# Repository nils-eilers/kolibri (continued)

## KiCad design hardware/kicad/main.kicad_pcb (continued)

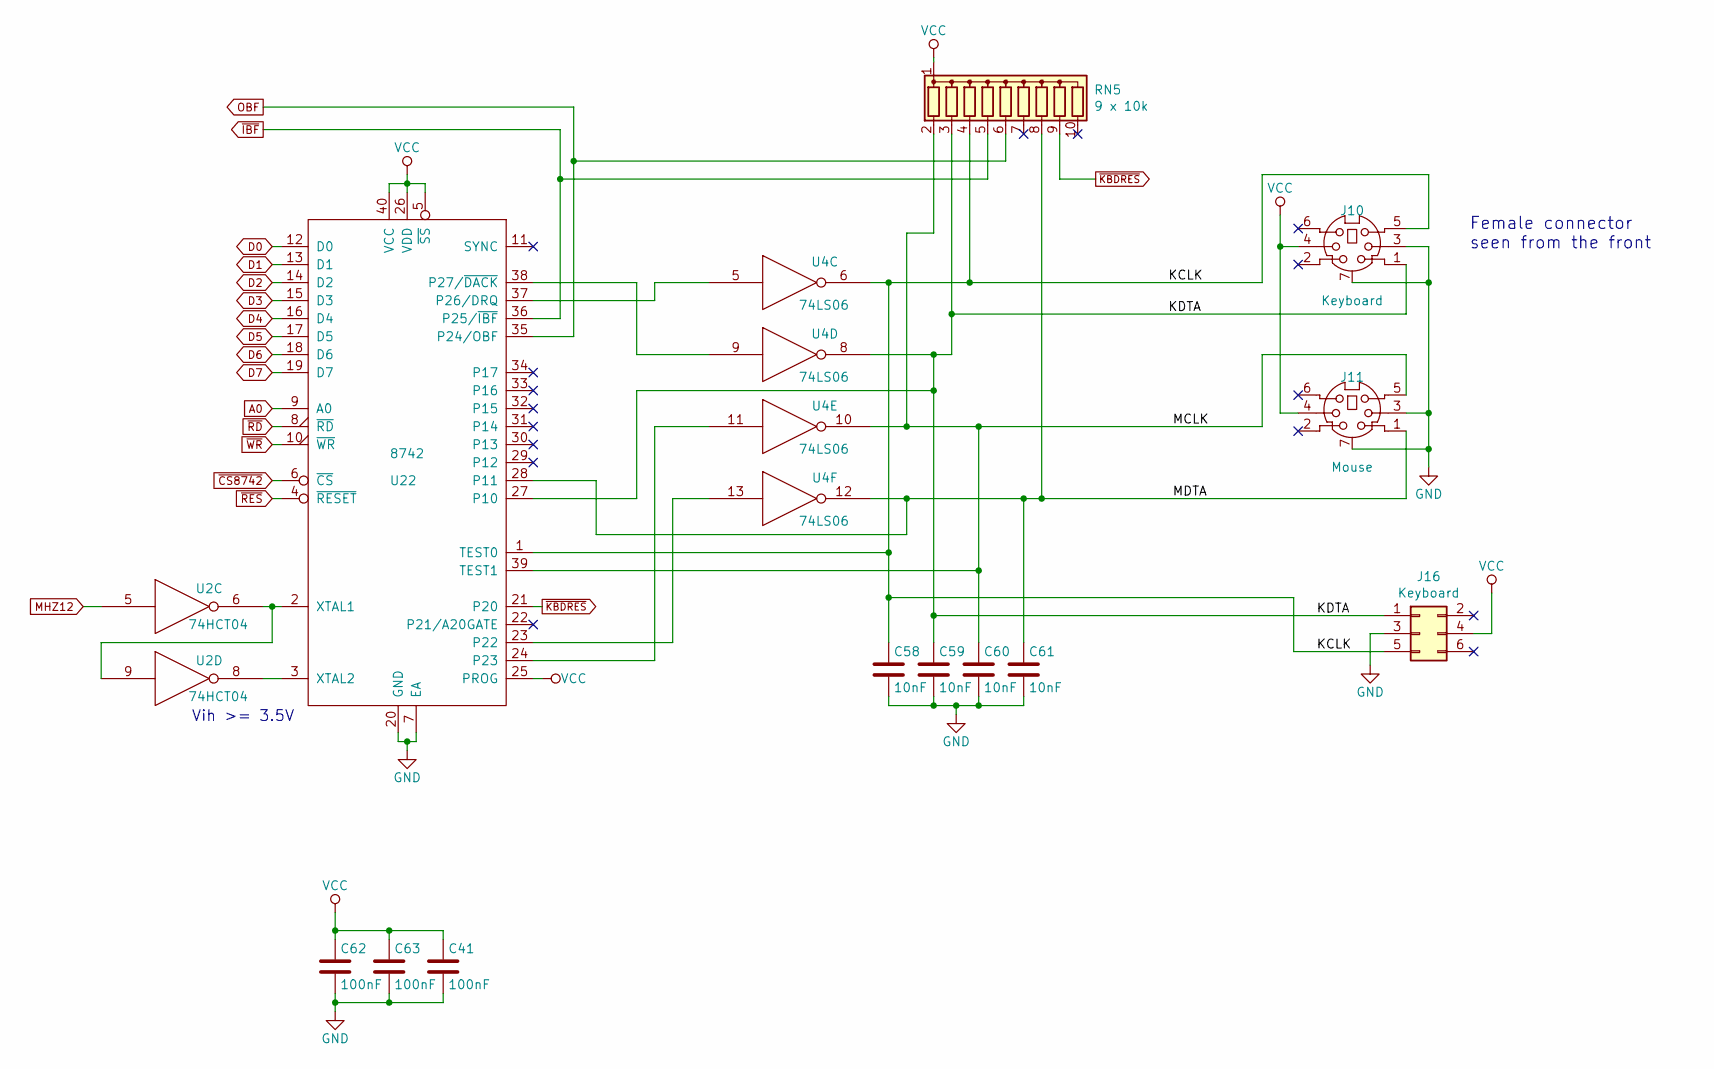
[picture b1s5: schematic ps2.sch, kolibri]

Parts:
C41, C62, C63: 100nF; KERKO-5
C58, C59, C60, C61: 10nF; KERKO-5
J10: Keyboard; EB-DIOS-M06
J11: Mouse; EB-DIOS-M06
J16: Keyboard; IDC-Header_2x03_P2.54mm_Vertical
RN5: 9 x 10k; R_Array_SIP10
U2: 74HCT04; DIP-14
U4: 74LS06; DIP-14
U22: 8742; DIP-40

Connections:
/Keyboard, Mouse/KCLK: C58.1, J10.5, J16.5, RN5.4 (R3), U4.6, U22.1 (TEST0)
/Keyboard, Mouse/KDTA: C59.1, J10.1, J16.1, RN5.3 (R2), U4.8, U22.27 (P10)
/Keyboard, Mouse/MCLK: C60.1, J11.5, RN5.2 (R1), U4.10, U22.39 (TEST1)
/Keyboard, Mouse/MDTA: C61.1, J11.1, RN5.8 (R7), U4.12, U22.28 (P11)
A0: U22.9 (A0); also elsewhere on the board
D0: U22.12 (D0); also elsewhere on the board
D1: U22.13 (D1); also elsewhere on the board
D2: U22.14 (D2); also elsewhere on the board
D3: U22.15 (D3); also elsewhere on the board
D4: U22.16 (D4); also elsewhere on the board
D5: U22.17 (D5); also elsewhere on the board
D6: U22.18 (D6); also elsewhere on the board
D7: U22.19 (D7); also elsewhere on the board
GND: C41.2, C58.2, C59.2, C60.2, C61.2, C62.2, C63.2, J10.3, J10.7 (Shell), J11.3, J11.7 (Shell), J16.3, U2.7 (GND), U4.7 (GND), U22.7 (EA), U22.20 (GND); also elsewhere on the board
MHZ12: U2.5; also elsewhere on the board
unnamed: U2.6, U2.9, U22.2 (XTAL1)
unnamed: U2.8, U22.3 (XTAL2)
unnamed: U4.13, U22.23 (P22)
unnamed: U4.11, U22.24 (P23)
unnamed: U4.5, U22.37 (P26/DRQ)
unnamed: U4.9, U22.38 (P27/~DACK)
OBF: RN5.6 (R5), U22.35 (P24/OBF); also elsewhere on the board
VCC: C41.1, C62.1, C63.1, J10.4, J11.4, J16.4, RN5.1 (common), U2.14 (VCC), U4.14 (VCC), U22.5 (~SS~), U22.25 (PROG), U22.26 (VDD), U22.40 (VCC); also elsewhere on the board
~CS8742: U22.6 (~CS); also elsewhere on the board
~IBF: RN5.5 (R4), U22.36 (P25/~IBF); also elsewhere on the board
~KBDRES: RN5.9 (R8), U22.21 (P20); also elsewhere on the board
~RD: U22.8 (~RD~); also elsewhere on the board
~RES: U22.4 (~RESET~); also elsewhere on the board
~WR: U22.10 (~WR~); also elsewhere on the board

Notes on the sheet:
Vih >= 3.5V
Female connector seen from the front

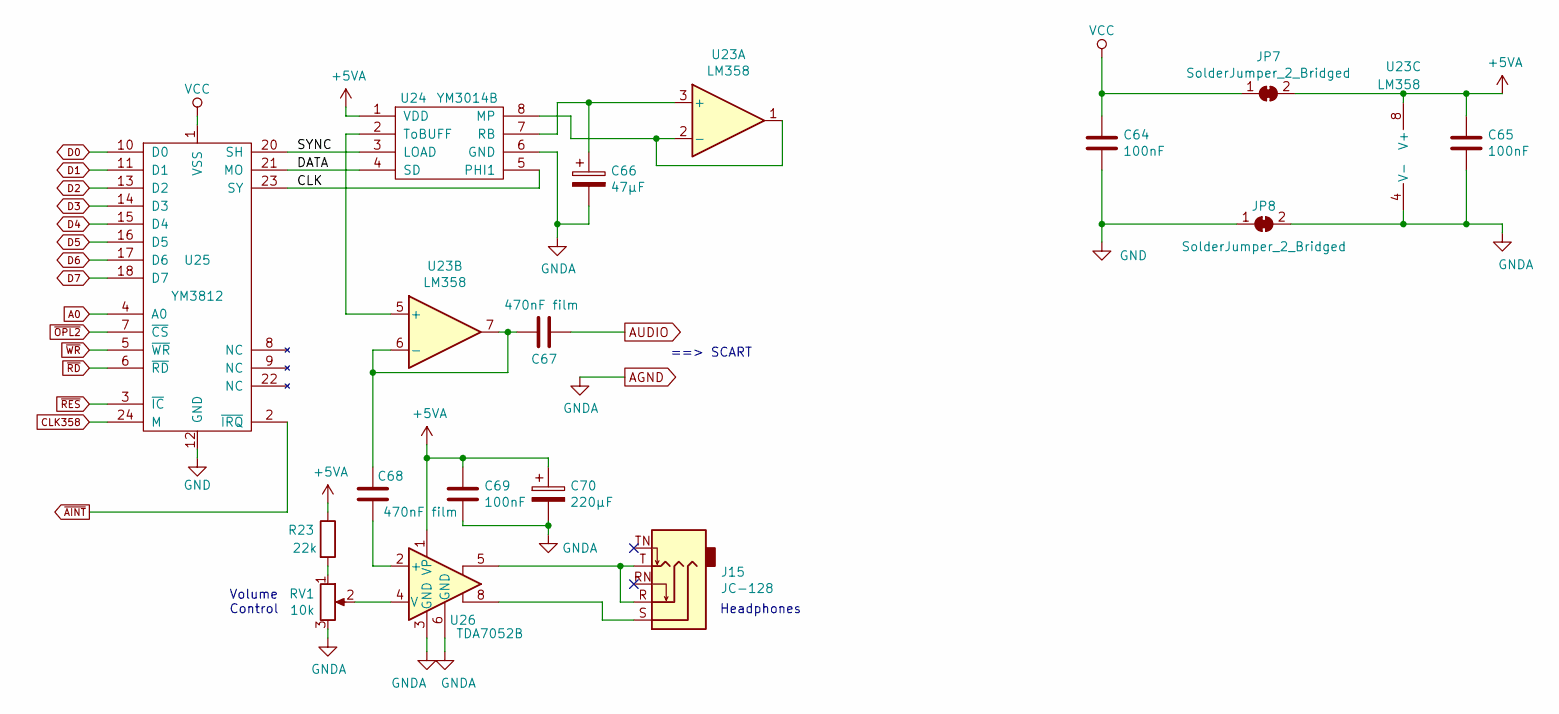
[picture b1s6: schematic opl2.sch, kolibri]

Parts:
C64, C65, C69: 100nF; KERKO-5
C66: 47µF; CP-2-5
C67, C68: 470nF film; C-FILM-5
C70: 220µF; CP-2-6
J15: JC-128
JP7, JP8: SolderJumper_2_Bridged; SolderJumper-2_P1.3mm_Bridged_RoundedPad1.0x1.5mm
R23: 22k; R
RV1: 10k; PT10H-THUMBWHEEL
U23: LM358; DIP-8
U24: YM3014B; DIP-8
U25: YM3812; DIP-24
U26: TDA7052B; DIP-8

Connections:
+5VA: C65.1, C69.1, C70.1, JP7.2 (B), R23.1, U23.8 (V+), U24.1 (VDD), U26.1 (VP)
/OPL2 sound/CLK: U24.5 (PHI1), U25.23 (SY)
/OPL2 sound/DATA: U24.4 (SD), U25.21 (MO)
/OPL2 sound/SYNC: U24.3 (LOAD), U25.20 (SH)
A0: U25.4 (A0); also elsewhere on the board
AGND: C65.2, C66.2, C69.2, C70.2, JP8.2 (B), RV1.3, U23.4 (V-), U24.6 (GND), U26.3 (GND), U26.6 (GND); also elsewhere on the board
AUDIO: C67.1; also elsewhere on the board
CLK358: U25.24 (M); also elsewhere on the board
D0: U25.10 (D0); also elsewhere on the board
D1: U25.11 (D1); also elsewhere on the board
D2: U25.13 (D2); also elsewhere on the board
D3: U25.14 (D3); also elsewhere on the board
D4: U25.15 (D4); also elsewhere on the board
D5: U25.16 (D5); also elsewhere on the board
D6: U25.17 (D6); also elsewhere on the board
D7: U25.18 (D7); also elsewhere on the board
GND: C64.2, JP8.1 (A), U25.12 (GND); also elsewhere on the board
unnamed: C66.1, U23.3 (+), U24.7 (RB)
unnamed: C67.2, C68.2, U23.6 (-), U23.7
unnamed: C68.1, U26.2 (+)
unnamed: J15.R, J15.T, U26.5
unnamed: J15.S, U26.8
unnamed: R23.2, RV1.1
unnamed: RV1.2, U26.4 (V)
unnamed: U23.1, U23.2 (-), U24.8 (MP)
unnamed: U23.5 (+), U24.2 (ToBUFF)
VCC: C64.1, JP7.1 (A), U25.1 (VSS); also elsewhere on the board
~AINT: U25.2 (~IRQ); also elsewhere on the board
~OPL2: U25.7 (~CS); also elsewhere on the board
~RD: U25.6 (~RD); also elsewhere on the board
~RES: U25.3 (~IC); also elsewhere on the board
~WR: U25.5 (~WR); also elsewhere on the board

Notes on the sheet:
==> SCART
Headphones
Volume Control

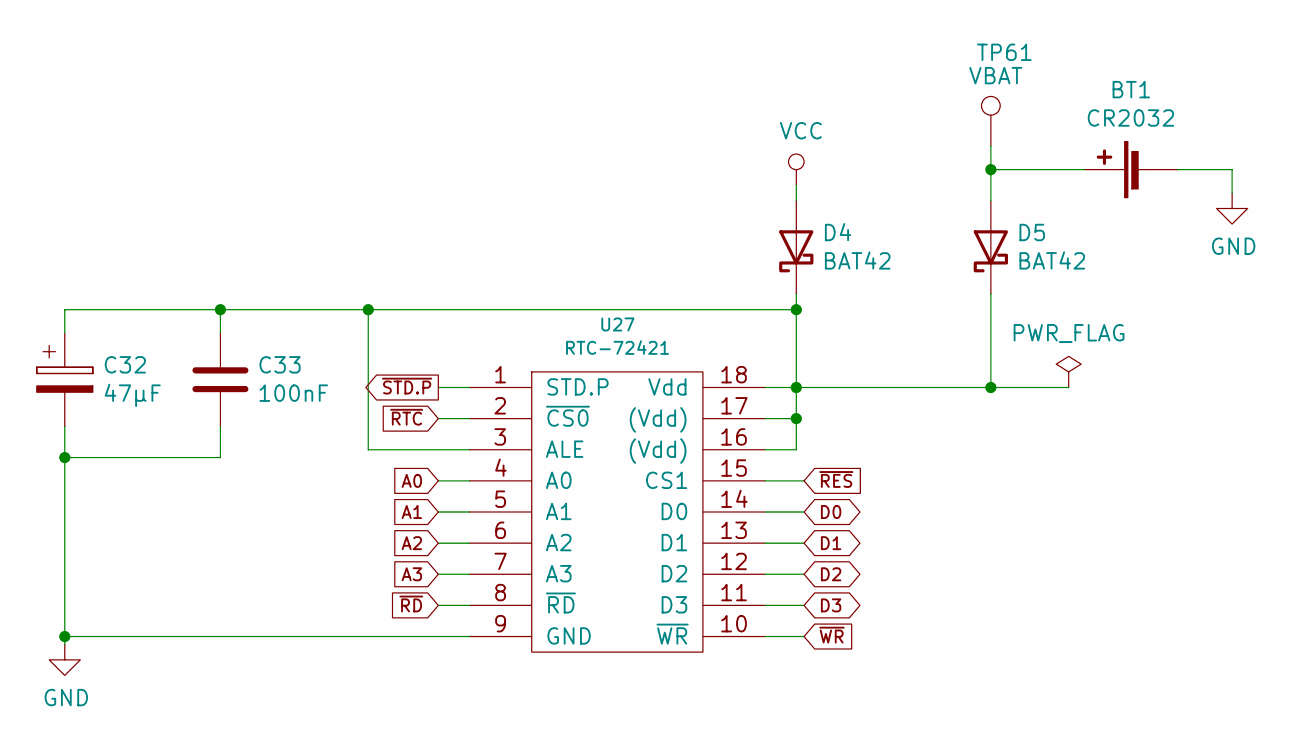
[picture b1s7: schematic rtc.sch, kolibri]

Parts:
BT1: CR2032; KZH20SMD
C32: 47µF; CP-2-5
C33: 100nF; KERKO-5
D4, D5: BAT42; DO35
TP61: VBAT; PINTST
U27: RTC-72421; DIP-18

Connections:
A0: U27.4 (A0); also elsewhere on the board
A1: U27.5 (A1); also elsewhere on the board
A2: U27.6 (A2); also elsewhere on the board
A3: U27.7 (A3); also elsewhere on the board
D0: U27.14 (D0); also elsewhere on the board
D1: U27.13 (D1); also elsewhere on the board
D2: U27.12 (D2); also elsewhere on the board
D3: U27.11 (D3); also elsewhere on the board
GND: BT1.2 (-), C32.2, C33.2, U27.9 (GND); also elsewhere on the board
unnamed: BT1.1 (+), D5.2 (A), TP61.1
unnamed: C32.1, C33.1, D4.1 (K), D5.1 (K), U27.3 (ALE), U27.16 ((Vdd)), U27.17 ((Vdd)), U27.18 (Vdd)
VCC: D4.2 (A); also elsewhere on the board
~RD: U27.8 (~RD); also elsewhere on the board
~RES: U27.15 (CS1); also elsewhere on the board
~RTC: U27.2 (~CS0); also elsewhere on the board
~STD.P: U27.1 (STD.P); also elsewhere on the board
~WR: U27.10 (~WR); also elsewhere on the board

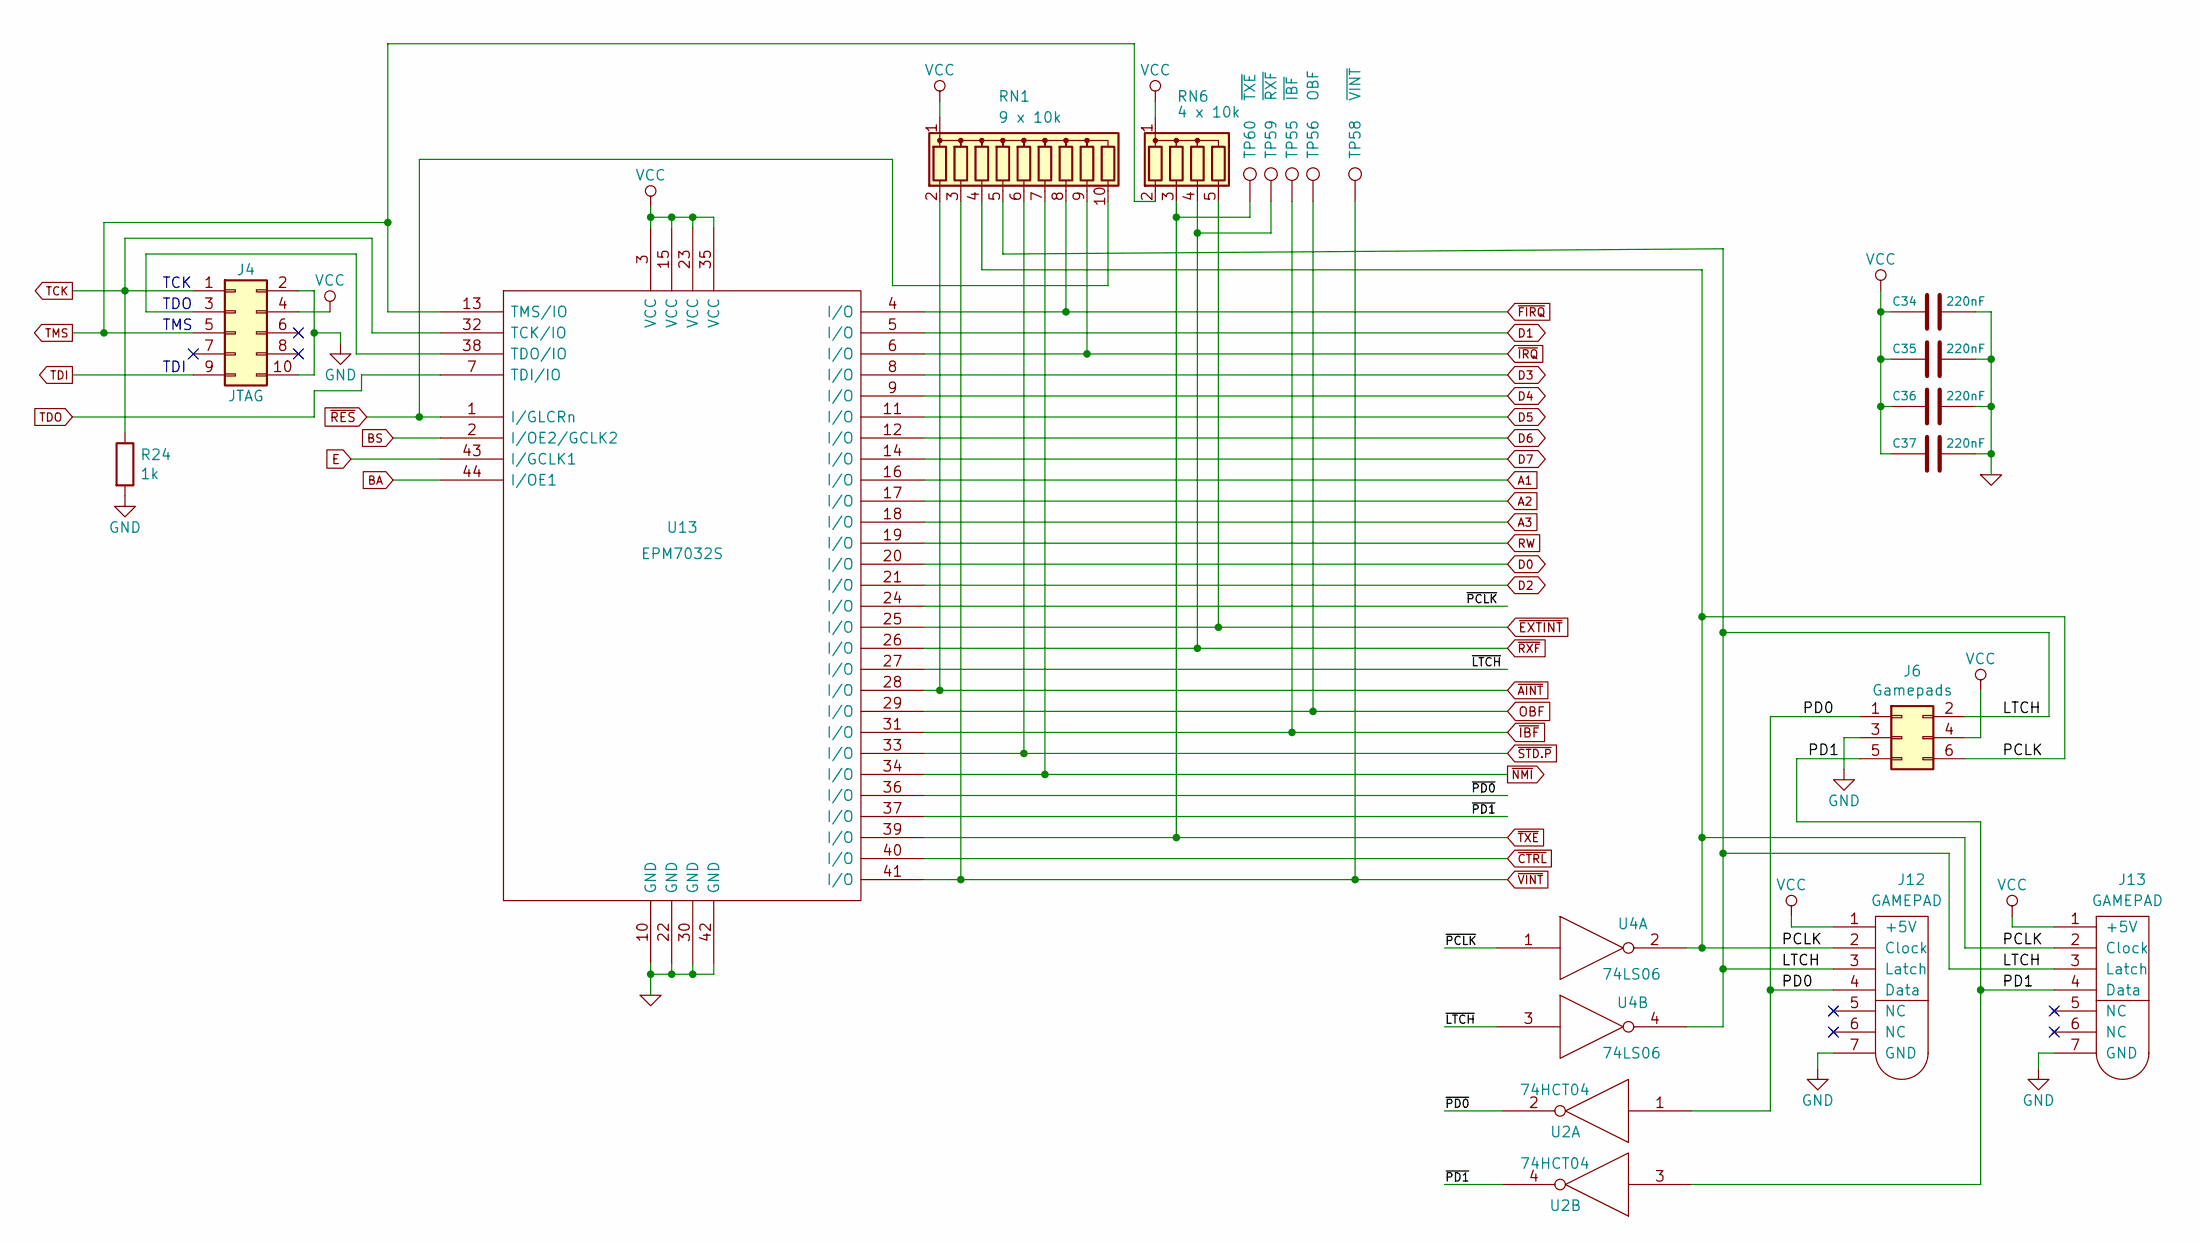
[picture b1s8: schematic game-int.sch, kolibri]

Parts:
C34, C35, C36, C37: 220nF; KERKO-5
J4: JTAG; WSL10G
J6: Gamepads; WSL_6W
J12, J13: GAMEPAD
R24: 1k; R
RN1: 9 x 10k; R_Array_SIP10
RN6: 4 x 10k; R_Array_SIP5
TP55: ~IBF; PINTST
TP56: OBF; PINTST
TP58: ~VINT; PINTST
TP59: ~RXF; PINTST
TP60: ~TXE; PINTST
U2: 74HCT04; DIP-14
U4: 74LS06; DIP-14
U13: EPM7032S; PLCC-44

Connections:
/Gamepads and Interrupts/LTCH: J6.2, J12.3 (Latch), J13.3 (Latch), RN1.5 (R4), U4.4
/Gamepads and Interrupts/PCLK: J6.6, J12.2 (Clock), J13.2 (Clock), RN1.4 (R3), U4.2
/Gamepads and Interrupts/PD0: J6.1, J12.4 (Data), U2.1
/Gamepads and Interrupts/PD1: J6.5, J13.4 (Data), U2.3
/Gamepads and Interrupts/~LTCH: U4.3, U13.27 (I/O)
/Gamepads and Interrupts/~PCLK: U4.1, U13.24 (I/O)
/Gamepads and Interrupts/~PD0: U2.2, U13.36 (I/O)
/Gamepads and Interrupts/~PD1: U2.4, U13.37 (I/O)
A1: U13.16 (I/O); also elsewhere on the board
A2: U13.17 (I/O); also elsewhere on the board
A3: U13.18 (I/O); also elsewhere on the board
BA: U13.44 (I/OE1); also elsewhere on the board
BS: U13.2 (I/OE2/GCLK2); also elsewhere on the board
D0: U13.20 (I/O); also elsewhere on the board
D1: U13.5 (I/O); also elsewhere on the board
D2: U13.21 (I/O); also elsewhere on the board
D3: U13.8 (I/O); also elsewhere on the board
D4: U13.9 (I/O); also elsewhere on the board
D5: U13.11 (I/O); also elsewhere on the board
D6: U13.12 (I/O); also elsewhere on the board
D7: U13.14 (I/O); also elsewhere on the board
E: U13.43 (I/GCLK1); also elsewhere on the board
GND: C34.2, C35.2, C36.2, C37.2, J4.2, J4.10, J6.3, J12.7 (GND), J13.7 (GND), R24.2, U2.7 (GND), U4.7 (GND), U13.10 (GND), U13.22 (GND), U13.30 (GND), U13.42 (GND); also elsewhere on the board
unnamed: J4.3, U13.38 (TDO/IO)
OBF: TP56.1, U13.29 (I/O); also elsewhere on the board
RW: U13.19 (I/O)
TCK: J4.1, R24.1, U13.32 (TCK/IO); also elsewhere on the board
TDI: J4.9; also elsewhere on the board
TDO: U13.7 (TDI/IO); also elsewhere on the board
TMS: J4.5, RN6.2 (R1), U13.13 (TMS/IO); also elsewhere on the board
VCC: C34.1, C35.1, C36.1, C37.1, J4.4, J6.4, J12.1 (+5V), J13.1 (+5V), RN1.1 (common), RN6.1 (common), U2.14 (VCC), U4.14 (VCC), U13.3 (VCC), U13.15 (VCC), U13.23 (VCC), U13.35 (VCC); also elsewhere on the board
~AINT: RN1.2 (R1), U13.28 (I/O); also elsewhere on the board
~CTRL: U13.40 (I/O); also elsewhere on the board
~EXTINT: RN6.5 (R4), U13.25 (I/O); also elsewhere on the board
~FIRQ: RN1.8 (R7), U13.4 (I/O); also elsewhere on the board
~IBF: TP55.1, U13.31 (I/O); also elsewhere on the board
~IRQ: RN1.9 (R8), U13.6 (I/O); also elsewhere on the board
~NMI: RN1.7 (R6), U13.34 (I/O); also elsewhere on the board
~RES: RN1.10 (R9), U13.1 (I/GLCRn); also elsewhere on the board
~RXF: RN6.4 (R3), TP59.1, U13.26 (I/O); also elsewhere on the board
~STD.P: RN1.6 (R5), U13.33 (I/O); also elsewhere on the board
~TXE: RN6.3 (R2), TP60.1, U13.39 (I/O); also elsewhere on the board
~VINT: RN1.3 (R2), TP58.1, U13.41 (I/O); also elsewhere on the board

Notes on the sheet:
TCK
TDO
TMS
TDI

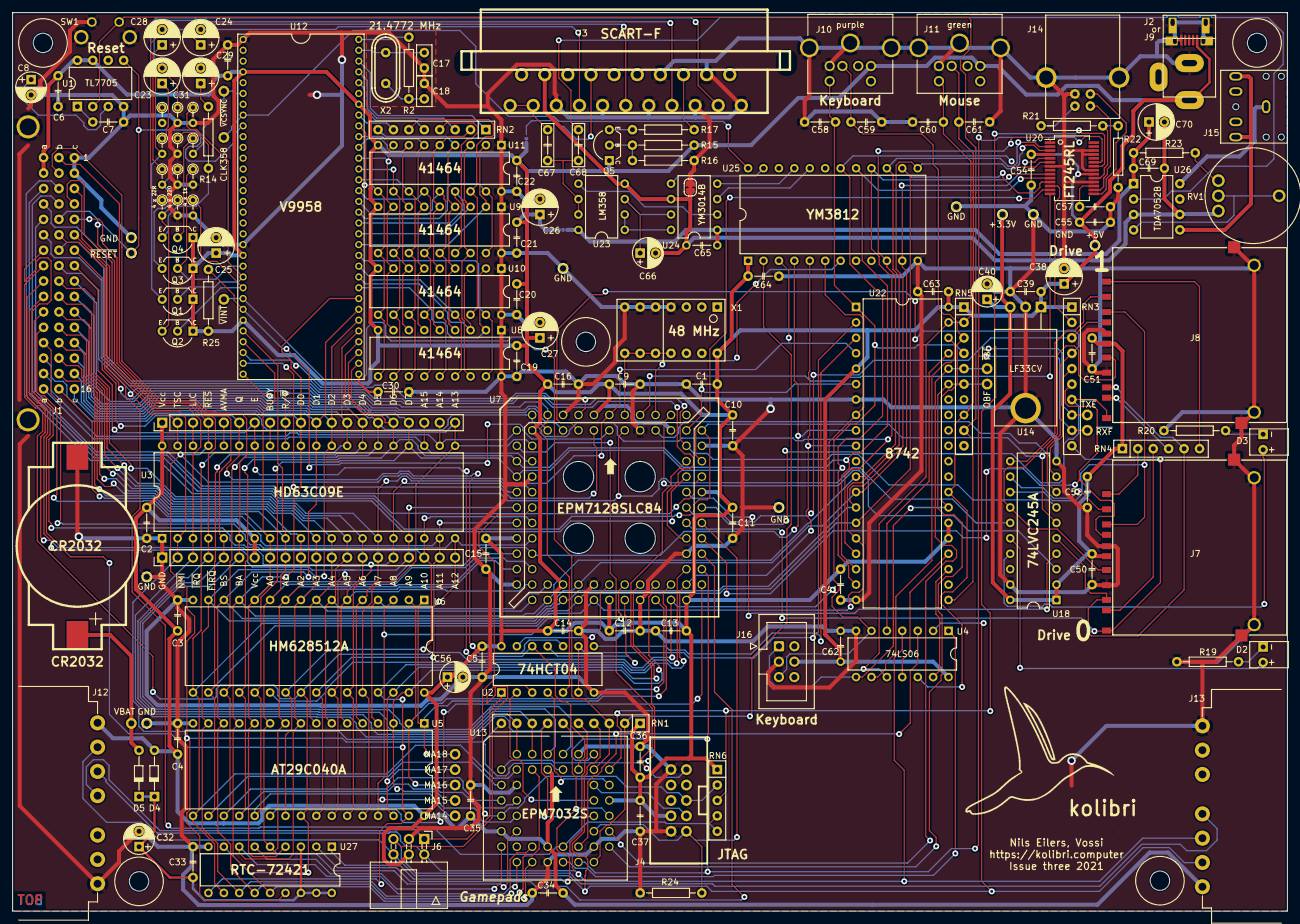
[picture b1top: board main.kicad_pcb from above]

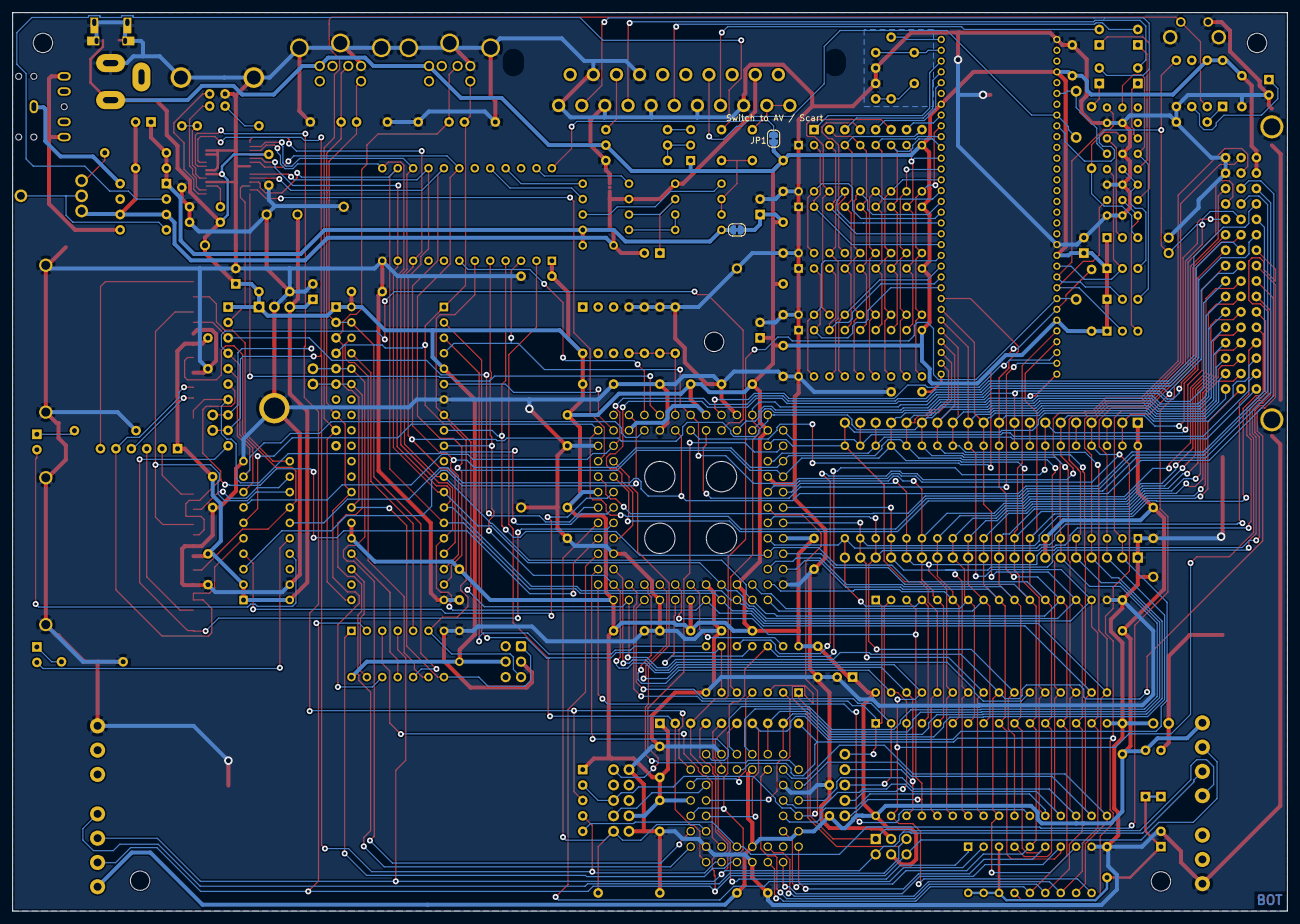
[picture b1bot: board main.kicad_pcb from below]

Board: 2 copper layers, 210.0 x 148.0 mm, 175 parts (2 on the bottom side), 196 nets.

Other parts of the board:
MH1, MH2, MH3, MH4, MH5: M3x6 + DI 8MM; M3-MOUNTHOLE

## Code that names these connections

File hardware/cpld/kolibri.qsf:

# -------------------------------------------------------------------------- #
#
# Copyright (C) 1991-2013 Altera Corporation
# Your use of Altera Corporation's design tools, logic functions 
# and other software and tools, and its AMPP partner logic 
# functions, and any output files from any of the foregoing 
# (including device programming or simulation files), and any 
# associated documentation or information are expressly subject 
# to the terms and conditions of the Altera Program License 
# Subscription Agreement, Altera MegaCore Function License 
# Agreement, or other applicable license agreement, including, 
# without limitation, that your use is for the sole purpose of 
# programming logic devices manufactured by Altera and sold by 
# Altera or its authorized distributors.  Please refer to the 
# applicable agreement for further details.
#
# -------------------------------------------------------------------------- #
#
# Quartus II 64-Bit
# Version 13.0.1 Build 232 06/12/2013 Service Pack 1 SJ Web Edition
# Date created = 00:44:14  April 05, 2018
#
# -------------------------------------------------------------------------- #
#
# Notes:
#
# 1) The default values for assignments are stored in the file:
#		kolibri_assignment_defaults.qdf
#    If this file doesn't exist, see file:
#		assignment_defaults.qdf
#
# 2) Altera recommends that you do not modify this file. This
#    file is updated automatically by the Quartus II software
#    and any changes you make may be lost or overwritten.
#
# -------------------------------------------------------------------------- #


set_global_assignment -name FAMILY MAX7000S
set_global_assignment -name DEVICE "EPM7128SLC84-15"
set_global_assignment -name TOP_LEVEL_ENTITY kolibri
set_global_assignment -name ORIGINAL_QUARTUS_VERSION "13.0 SP1"
set_global_assignment -name PROJECT_CREATION_TIME_DATE "00:44:14  APRIL 05, 2018"
set_global_assignment -name LAST_QUARTUS_VERSION "13.0 SP1"
set_global_assignment -name PROJECT_OUTPUT_DIRECTORY output_files
set_global_assignment -name DEVICE_FILTER_PACKAGE PLCC
set_global_assignment -name DEVICE_FILTER_PIN_COUNT 84
set_global_assignment -name ERROR_CHECK_FREQUENCY_DIVISOR "-1"
set_global_assignment -name MIN_CORE_JUNCTION_TEMP 0
set_global_assignment -name MAX_CORE_JUNCTION_TEMP 85
set_global_assignment -name EDA_SIMULATION_TOOL "ModelSim-Altera (SystemVerilog)"
set_global_assignment -name EDA_OUTPUT_DATA_FORMAT "SYSTEMVERILOG HDL" -section_id eda_simulation
set_global_assignment -name TIMEQUEST_REPORT_SCRIPT_INCLUDE_DEFAULT_ANALYSIS OFF
set_global_assignment -name DEVICE_FILTER_SPEED_GRADE 15
set_location_assignment PIN_57 -to nRAMCS
set_location_assignment PIN_54 -to nROMCS
set_location_assignment PIN_10 -to RW
set_location_assignment PIN_29 -to A[0]
set_location_assignment PIN_28 -to A[1]
set_location_assignment PIN_31 -to A[2]
set_location_assignment PIN_30 -to A[3]
set_location_assignment PIN_33 -to A[4]
set_location_assignment PIN_36 -to A[5]
set_location_assignment PIN_34 -to A[6]
set_location_assignment PIN_21 -to A[7]
set_location_assignment PIN_20 -to A[8]
set_location_assignment PIN_22 -to A[9]
set_location_assignment PIN_25 -to A[10]
set_location_assignment PIN_24 -to A[11]
set_location_assignment PIN_27 -to A[12]
set_location_assignment PIN_15 -to A[13]
set_location_assignment PIN_12 -to A[14]
set_location_assignment PIN_17 -to A[15]
set_location_assignment PIN_18 -to D[7]
set_location_assignment PIN_16 -to D[6]
set_location_assignment PIN_11 -to D[5]
set_location_assignment PIN_41 -to D[4]
set_location_assignment PIN_39 -to D[3]
set_location_assignment PIN_37 -to D[2]
set_location_assignment PIN_40 -to D[1]
set_location_assignment PIN_35 -to D[0]
set_global_assignment -name SYNTH_TIMING_DRIVEN_SYNTHESIS OFF

set_global_assignment -name MAX7000_DEVICE_IO_STANDARD TTL
set_location_assignment PIN_83 -to MHZ48
set_location_assignment PIN_51 -to nRD
set_location_assignment PIN_55 -to nWR
set_global_assignment -name VERILOG_FILE clock.v
set_location_assignment PIN_44 -to nE
set_location_assignment PIN_6 -to nSD0
set_location_assignment PIN_45 -to nQ
set_location_assignment PIN_80 -to nSD1
set_location_assignment PIN_4 -to nCSR
set_location_assignment PIN_5 -to nCSW
set_location_assignment PIN_2 -to nWAIT
set_location_assignment PIN_79 -to nOPL2
set_location_assignment PIN_61 -to nIOEN
set_location_assignment PIN_70 -to nRD245
set_location_assignment PIN_73 -to MOSI
set_location_assignment PIN_74 -to SCLK
set_location_assignment PIN_58 -to nRTC
set_location_assignment PIN_76 -to nCS8742
set_location_assignment PIN_9 -to MHZ12
set_location_assignment PIN_81 -to WR245
set_location_assignment PIN_84 -to MISO
set_location_assignment PIN_23 -to TMS
set_location_assignment PIN_62 -to TCK
set_location_assignment PIN_14 -to TDI
set_location_assignment PIN_71 -to TDO
set_location_assignment PIN_1 -to nRES
set_global_assignment -name CDF_FILE output_files/kolibri.cdf
set_location_assignment PIN_8 -to TSC
set_location_assignment PIN_46 -to MA14
set_location_assignment PIN_48 -to MA[17]
set_location_assignment PIN_49 -to MA[16]
set_location_assignment PIN_50 -to MA15
set_location_assignment PIN_52 -to MA[18]
set_location_assignment PIN_56 -to nCTRL
set_location_assignment PIN_60 -to CD0
set_location_assignment PIN_63 -to WP0
set_location_assignment PIN_64 -to CD1
set_location_assignment PIN_65 -to WP1
set_location_assignment PIN_77 -to LED1
set_location_assignment PIN_69 -to nSPI1
set_location_assignment PIN_68 -to nSPI2
set_location_assignment PIN_67 -to LED0
set_global_assignment -name VERILOG_FILE kolibri.v

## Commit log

2020-02-10 add VDC manual
2020-02-10 replace VDC manual
2020-02-10 add V9958 register description
2020-02-10 add V9958 tutorial
2020-02-10 collect V9958 papers in directory
2020-02-11 start kolibri manual
2020-02-12 start BIOS chapter
2020-02-12 remove manual.pdf
2020-02-12 change bios.tex
2020-02-13 as9 language = assembly
2020-02-13 Add .gitigore and Makefile
2020-02-13 Create same binary for emulator and physical machine
2020-02-13 Add systemfont and font tools
2020-02-13 Ignore generated binaries but not binary font files
2020-02-13 Add README.md
2020-02-13 changed VDP-Port DEFS
2020-02-13 first vdp routines
2020-02-13 saved some space with WAIT6US sub
2020-02-13 Use .fon file extension for fonts, central .gitignore file
2020-02-14 vdp: loadfont, display on/off
2020-02-16 new SWI handler
2020-02-16 monitor commands r and m
2020-02-16 fix CMPR bug in emulator
2020-02-16 update monitor
2020-02-16 optimize and comment monitor
2020-02-16 fix trap and div0 errors in emu
2020-02-17 start description of MMU in manual
2020-02-17 updated vdp.as9 and integrated in firmware
2020-02-17 fix definitions
2020-02-17 added VDP_ClearWindow, bugfix VDP_init
2020-02-17 added VDP_SetColor
2020-02-17 align definitions
2020-02-17 prefix names of I/O addresses with 'IO_'
2020-02-17 added VDP_PutChar (without scrolling
2020-02-17 added VDP_PutChar bugfix(without scrolling
2020-02-17 manual: refer to proper definitons file
2020-02-17 manual: more work on the MMU description
2020-02-17 manual: make the code example executable
    All code examples should actually be executable.
    It is clear to an experienced assembly programmer
    that the former example was just meant as an
    example but a less experienced person might
    just copy and paste that example and experience
    a failire because of the string constant
2020-02-17 Reformat source files
2020-02-17 Add .vimrc settings for .as9 source files
    - Tab size is 8
    - expand tabs to spaces
    - show line numbers
    - enable syntax highlighting for 6309 assembly
2020-02-18 converted tabs to spaces
2020-02-18 reserved line scrollbuffer
2020-02-18 added scoll window
2020-02-18 bugfix vdp scrolling
2020-02-19 added cursor move, changet set color
2020-02-19 optimized put char-move right
2020-02-19 add NCURSES emulator windows for screen and debug
2020-02-19 change CR/LF to LF
2020-02-19 restore PREFIX of emu Makefile to /usr/local
2020-02-20 added cursor
2020-02-20 added delete and backspace
2020-02-20 added Set Cursor, Get Char, Get Line
2020-02-20 added Insert
2020-02-21 some vdp optimizations
2020-02-21 Some small ncurses additions
    - scroll windows
    - restore screen and terminal settings at exit
2020-02-21 Automatic size for debug window
2020-02-24 adapt emu debug window to terminal size
2020-02-24 display VDP access in emu debug window
2020-02-24 switch off debug watch addresses in ncurses mode
2020-02-24 make compilation of screen.h conditional
2020-02-24 setcursor readchar ok
2020-02-25 fix emu display
2020-02-25 fixed scroll-bug
2020-02-25 fixed scroll-bug space
2020-02-25 clear screen with space
2020-02-25 dual-parameter in E/F, SetWindow
2020-02-25 new function VDP_GetCursor
2020-02-26 Include VDP-routines in BIOS, add VDP greeter
2020-02-26 Remove superfluous VDP_ClearWindow
2020-02-26 minor fixes
2020-02-26 implement VDP_Out and jumptable for control codes
2020-02-26 add entry CursorDown
2020-02-26 added tab, cr, lf
2020-02-26 changed VDP_TAB to VDP_TABLE
2020-02-29 update VDP_TABLE
2020-02-29 prepare EMU for ncurses
2020-02-29 prepare for ncurses
2020-03-03 Fix firmware Makefile for 32/32K system
2020-03-03 Match vimrc syntax file name with file provided by BS9
2020-03-06 Revert "Fix firmware Makefile for 32/32K system"
    This reverts commit b68e4203ec9ceff198834643d5c6b88341d37af0.
2020-03-06 First signs of life
2020-03-06 Add Verilog code for kolibri's CPLD
2020-03-08 use BIOS_EMU_Flag in USB_In
2020-03-09 add routine for loading program files to emulator
2020-03-09 add program load option -p to emu
2020-03-09 read program load address in big endian order
2020-03-12 use load address from PRG files
2020-03-14 add missing zero register to emu
2020-03-15 added color VDP.AS9 - insert+delete not finished
2020-03-15 fixed cursor up+down
2020-03-16 Fix serial USB I/O
2020-03-16 Add FLUSH SWI to drop any superfluous characters
2020-03-16 Fix monitor ':' command to enable the entry of 16 bytes
2020-03-18 vdp delete with color
2020-03-18 adjust S register value in display
2020-03-19 ascii-loop in a window, x still not working
2020-03-19 start vdpdemo with g 80c7
2020-03-19 fix hexdump ($7f is unprintable)
2020-03-20 Rewrite memory allocations
2020-03-20 Add VDP_PutS
2020-03-20 Fix re-write of memory allocations
2020-03-20 insert with color table fnished and tested
2020-03-22 update VDP table
2020-03-22 system stack in vdp-routines
2020-03-23 Move examples to new directory test-demo
2020-03-23 Ignore S-record files
    Basically, generated files shouldn't get checked in
2020-03-23 New monitor command 'L': load S19 files
2020-03-23 De-noise Makefile
2020-03-23 Ignore Altera Quartus' qws file
2020-03-23 monitor: move prompt to proper position
2020-03-23 Fix monitor 'L'oad CR/CRLF issue
    Loading does work now on both the real machine
    as well as on the emulator. It is a pity that
    this is another example of where the emulator
    behaves differently from the real machine.
2020-03-24 Fix storage path for code example
2020-03-24 optimized vdp.as9
2020-03-26 add monitor command (E)xecute
2020-04-03 ds_store für mac zugefügt
2020-04-03 Revert "ds_store für mac zugefügt"
    One "*.DS_Store" per .gitignore should be enough
    This reverts commit c900eed3490cd78c70cd3bf73c1fb4f32f091f39.
2020-04-03 added 24MHz to CPLD
2020-04-03 removed .DS_Store
2020-04-03 sh rights
2020-04-06 Load S-Record file if boot switch is pressed
2020-04-06 CPLD: add some missing chip select signals
2020-04-07 Use TIM command (test in memory)
2020-04-07 Add real time clock commands
2020-04-07 Fix a comment about the date and time format for T=
2020-04-08 prepare unassembler implementation
2020-04-09 Add Wannabe Power Chime
    Pressing Ctrl-G while editing will ring
    the bell also
2020-04-10 add unassembler variables
2020-04-10 unassembler works for 6809 instructions
2020-04-10 fix registernames in unassembler
2020-04-11 monitor .u with no address
2020-04-12 use packed menmonics table
2020-04-12 use 5 character for mnemonics
2020-04-12 implement some 6309 instructions in unassembler
2020-04-12 more 6309 codes for unassembler
2020-04-13 yet more unassembler code
2020-04-13 more unassembler stuff
2020-04-14 unassemble register/direct page bit operations
2020-04-14 Unassembler supports now ALL 6309 codes
2020-04-15 spend some $ :-)
2020-04-15 Print 5bit offsets as signed decimal
2020-04-15 fix TIM bug in emulator
2020-04-15 Fix boot switch handling
2020-04-15 emu: remove dead code
    Flags and CLK are already handled by and() in TIM handling
    starting at line 5470
2020-04-15 emu: add option -b to handle boot switch
    -b --> boot switch pressed
    -b+ --> boot switch pressed
    -b- --> boot switch not pressed
    -b option not given (the default) --> boot switch not pressed
2020-04-15 fix modes involving ,W
2020-04-15 cleanup unas.as9
2020-04-16 Prepare FPU support
2020-04-16 optimize unassembler
2020-04-17 Add SPI bus support
2020-04-17 Ignore .bak backup files
2020-04-17 optimize spi.as9
2020-04-17 fix SPI_MOSI_HI
2020-04-18 optimize spi.as9 again
2020-04-18 SPI mode 0 (CPHA=0, CPOL=0) is the proper setting to control MMC/SDC
2020-04-19 add help command to monitor
2020-04-19 implement monitor fill command
2020-04-19 add command 'o' = find Occurance to monitor
2020-04-19 monitor modify memory accepts now less than 16 bytes
2020-04-19 optimize monitor 'o' command
2020-04-19 allow quoted search string in monitor command o
2020-04-19 optimize monitor
2020-04-20 Monitor ':' command verifies writing to RAM
2020-04-20 add monitor command [C] Copy
2020-04-21 prepare BASIC
2020-04-21 use page 3 as direct page for monitor
2020-04-22 add error checks to monitor routines
2020-04-25 CPLD: output MISO only during valid memory accesses (E=high)
2020-04-25 Type <RETURN> to enter monitor: machine version
2020-04-25 CPLD: add missing pin assignment for 68882 chip select
2020-04-25 CPLD: add /STROBE pulse for MMU
2020-04-25 fix m and u quirks
2020-04-25 fix m
2020-04-25 CPLD: select MMU configuration only by write accesses
2020-04-25 CPLD: enable/disable MMU map mode
    Note: chip select signals are still missing in map mode
2020-04-25 CPLD: reformat and comment verilog source
2020-04-25 rename source file
2020-04-25 opl2.as9: get rid of vdp.as9 as a requirement
2020-04-25 fix whatsyourname demo
2020-04-25 Rework firmware build process
2020-04-26 firmware: scatter some crumbs of bread
    Store start address at the beginning of each page
    to simplify MMU tests
2020-04-26 CPLD: chip select signals for MMU in map mode
2020-05-02 Add config file for minicom terminal program
2020-05-10 monitor: fix help text
    The S19 load routine does not accept any addresses,
    these are stored in the individual S-records
2020-05-10 CPLD: generate chip select signals only while E=1
2020-05-18 start monitor chapter
2021-05-02 First PS/2 keyboard experiments
2021-05-02 New PCB: Issue Two
2021-05-02 Slightly update manual
2021-05-04 Some corrections for issue two
2021-05-06 Add Verilog project for second CPLD (Gamepads, Interrupts)
2021-05-06 Switch license to public domain/unlicense.org
2021-05-17 Fix CPLD pin assignments
2021-05-18 Clarify generation of chip select signals
    Doesn't create binary changes
2021-05-18 Rework I/O defs, especially for FT245 signals
2021-05-20 Minor firmware fixes
2021-05-22 Ignore KiCad backup files
2021-05-22 Ignore KiCad autosaved files
2021-05-22 Make LEDs work
2021-05-22 Remove workaround
2021-05-22 Rename some I/O ports
2021-05-23 Build a JTAG chain
    Thats just one JTAG connector for both CPLDs
2021-05-25 New PCB: Issue Three
2021-05-26 Update schematics to issue three board
2021-05-26 Keyboard Controller: restart (not from scratch)
2021-05-26 Remove false claim
2021-05-26 Update BILL OF MATERIALS for issue three board
